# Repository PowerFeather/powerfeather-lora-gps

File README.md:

## DIY LoRa + GPS Wing

This project is a LoRa + GPS wing that can be stacked on top (or below) of an ESP32-S3 PowerFeather to create a compact, low-power, solar + LiPo/Li-Ion powered node.

For more info, check the project log on [Hackaday](https://hackaday.io/project/198261-diy-esp32-solar-lora-gps-node).

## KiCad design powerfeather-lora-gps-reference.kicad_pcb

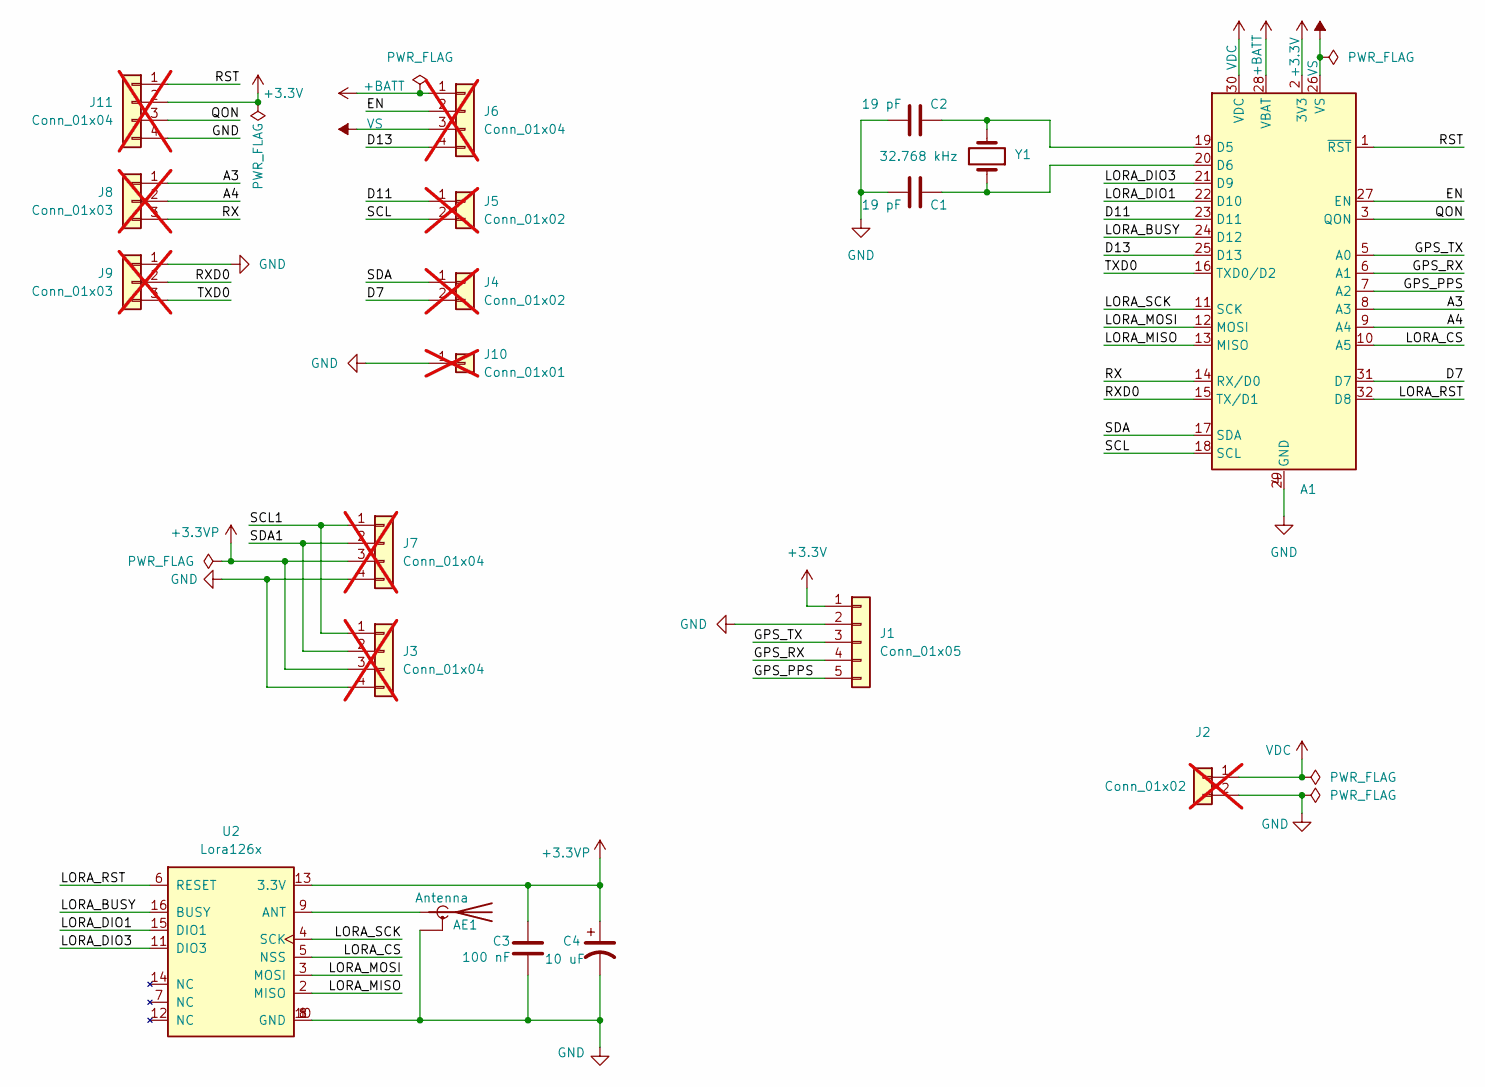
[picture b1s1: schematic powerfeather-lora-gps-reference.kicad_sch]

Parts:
A1: PowerFeather_Wing1; PowerFeather_Mainboard
AE1: Antenna; SMA_Edge
C1, C2: 19 pF; C_Disc_D4.3mm_W1.9mm_P5.00mm
C3: 100 nF; C_Disc_D4.3mm_W1.9mm_P5.00mm
C4: 10 uF; C_Radial_D4.0mm_H5.0mm_P1.50mm
J1: Conn_01x05; PinHeader_1x05_P2.54mm_Vertical
J2: Conn_01x02; TerminalBlock_TE_282834-2_1x02_P2.54mm_Horizontal; not fitted
J3, J7: Conn_01x04; PinHeader_1x04_P1.27mm_Vertical; not fitted
J4, J5: Conn_01x02; PinHeader_1x02_P2.54mm_Vertical; not fitted
J6, J11: Conn_01x04; PinHeader_1x04_P2.54mm_Vertical; not fitted
J8, J9: Conn_01x03; PinHeader_1x03_P2.54mm_Vertical; not fitted
J10: Conn_01x01; PinHeader_1x01_P2.54mm_Vertical; not fitted
U2: Lora126x
Y1: 32.768 kHz; Crystal_C38-LF_D3.0mm_L8.0mm_Horizontal

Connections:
+3.3V: A1.2 (3V3), J1.1, J11.2
+3.3VP: C3.1, C4.1, J3.3, J7.3, U2.13 (3.3V)
+BATT: A1.28 (VBAT), J6.1
/A3: A1.8 (A3), J8.1
/A4: A1.9 (A4), J8.2
/D7: A1.31 (D7), J4.2
/D11: A1.23 (D11), J5.1
/D13: A1.25 (D13), J6.4
/EN: A1.27 (EN), J6.2
/GPS_PPS: A1.7 (A2), J1.5
/GPS_RX: A1.6 (A1), J1.4
/GPS_TX: A1.5 (A0), J1.3
/LORA_BUSY: A1.24 (D12), U2.16 (BUSY)
/LORA_CS: A1.10 (A5), U2.5 (NSS)
/LORA_DIO1: A1.22 (D10), U2.15 (DIO1)
/LORA_DIO3: A1.21 (D9), U2.11 (DIO3)
/LORA_MISO: A1.13 (MISO), U2.2 (MISO)
/LORA_MOSI: A1.12 (MOSI), U2.3 (MOSI)
/LORA_RST: A1.32 (D8), U2.6 (RESET)
/LORA_SCK: A1.11 (SCK), U2.4 (SCK)
/QON: A1.3 (QON), J11.3
/RST: A1.1 (~RST), J11.1
/RX: A1.14 (RX/D0), J8.3
/RXD0: A1.15 (TX/D1), J9.2
/SCL: A1.18 (SCL), J5.2
/SCL1: J3.1, J7.1
/SDA: A1.17 (SDA), J4.1
/SDA1: J3.2, J7.2
/TXD0: A1.16 (TXD0/D2), J9.3
GND: A1.4 (GND), A1.29 (GND), AE1.2 (Shield), C1.2, C2.2, C3.2, C4.2, J1.2, J2.2, J3.4, J7.4, J9.1, J10.1, J11.4, U2.1 (GND), U2.8 (GND), U2.10 (GND)
unnamed: A1.19 (D5), C2.1, Y1.2
unnamed: A1.20 (D6), C1.1, Y1.1
unnamed: AE1.1 (A), U2.9 (ANT)
VDC: A1.30 (VDC), J2.1
VS: A1.26 (VS), J6.3

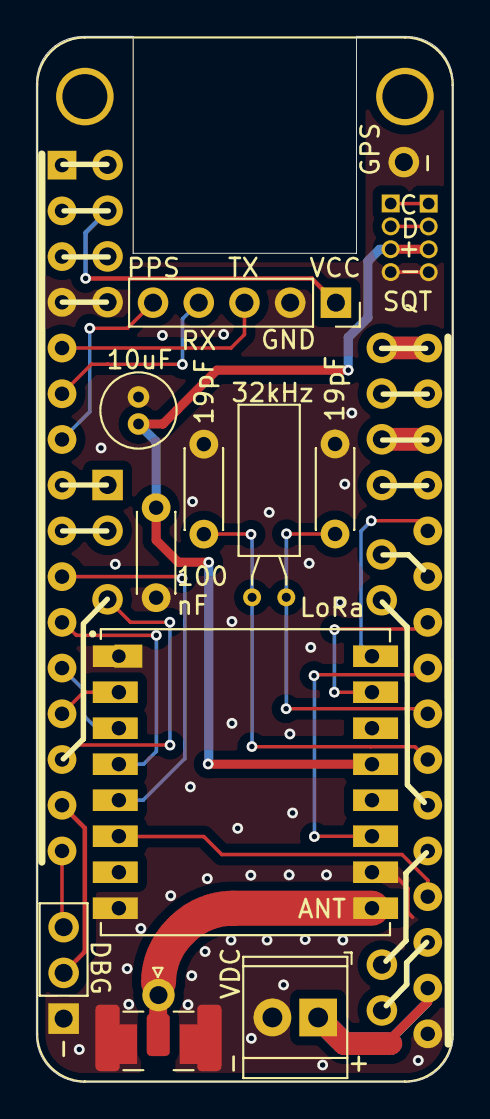
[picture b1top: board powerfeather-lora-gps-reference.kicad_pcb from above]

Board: 2 copper layers, 23.1 x 58.1 mm, 19 parts (1 on the bottom side), 35 nets.

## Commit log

2024-08-26 Add symbol and footprint lib
2024-08-27 Add powerfeather common submodule lib
2024-08-27 Add gitignore
2024-08-27 Add powerfeather-kicad-lib
2024-08-27 Remove some unused local symbols
2024-08-27 Fixes syms and footprints
2024-08-27 Resetting some components for layout
2024-08-27 Rearrange rough layout again
2024-08-27 Add antenna marker
2024-08-27 Reroute traces
2024-08-27 Fix some silkscreen
2024-08-27 Mark main pins in silkscreen
2024-08-27 Add rule keepout for SMA
2024-08-27 Add duplicate indicator at the back
2024-08-28 Output files for fabrication
2024-10-15 Change antenna trace width according to calc
    - 4.5 dielectric constant
    - H=1.6
    - 865/920 Mhz
    - S=0.5
2024-10-16 Add page info
2024-10-16 Add readme
2024-10-16 Add schematic pdf output
